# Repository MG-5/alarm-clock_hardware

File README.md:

# alarm-clock_v3
Hardware for alarm clock with VFD display

### Requirements for rev 1.0
* 24V input
* efficient boost converter up to 40V
* control VFD display with multiplexing & dimming
* control 24V CCT-LED strip (cold/neutral/warm white) with PWM
* I²C interface
  * DS3231 as RTC
* connection to ESP (UART)
* battery-backup

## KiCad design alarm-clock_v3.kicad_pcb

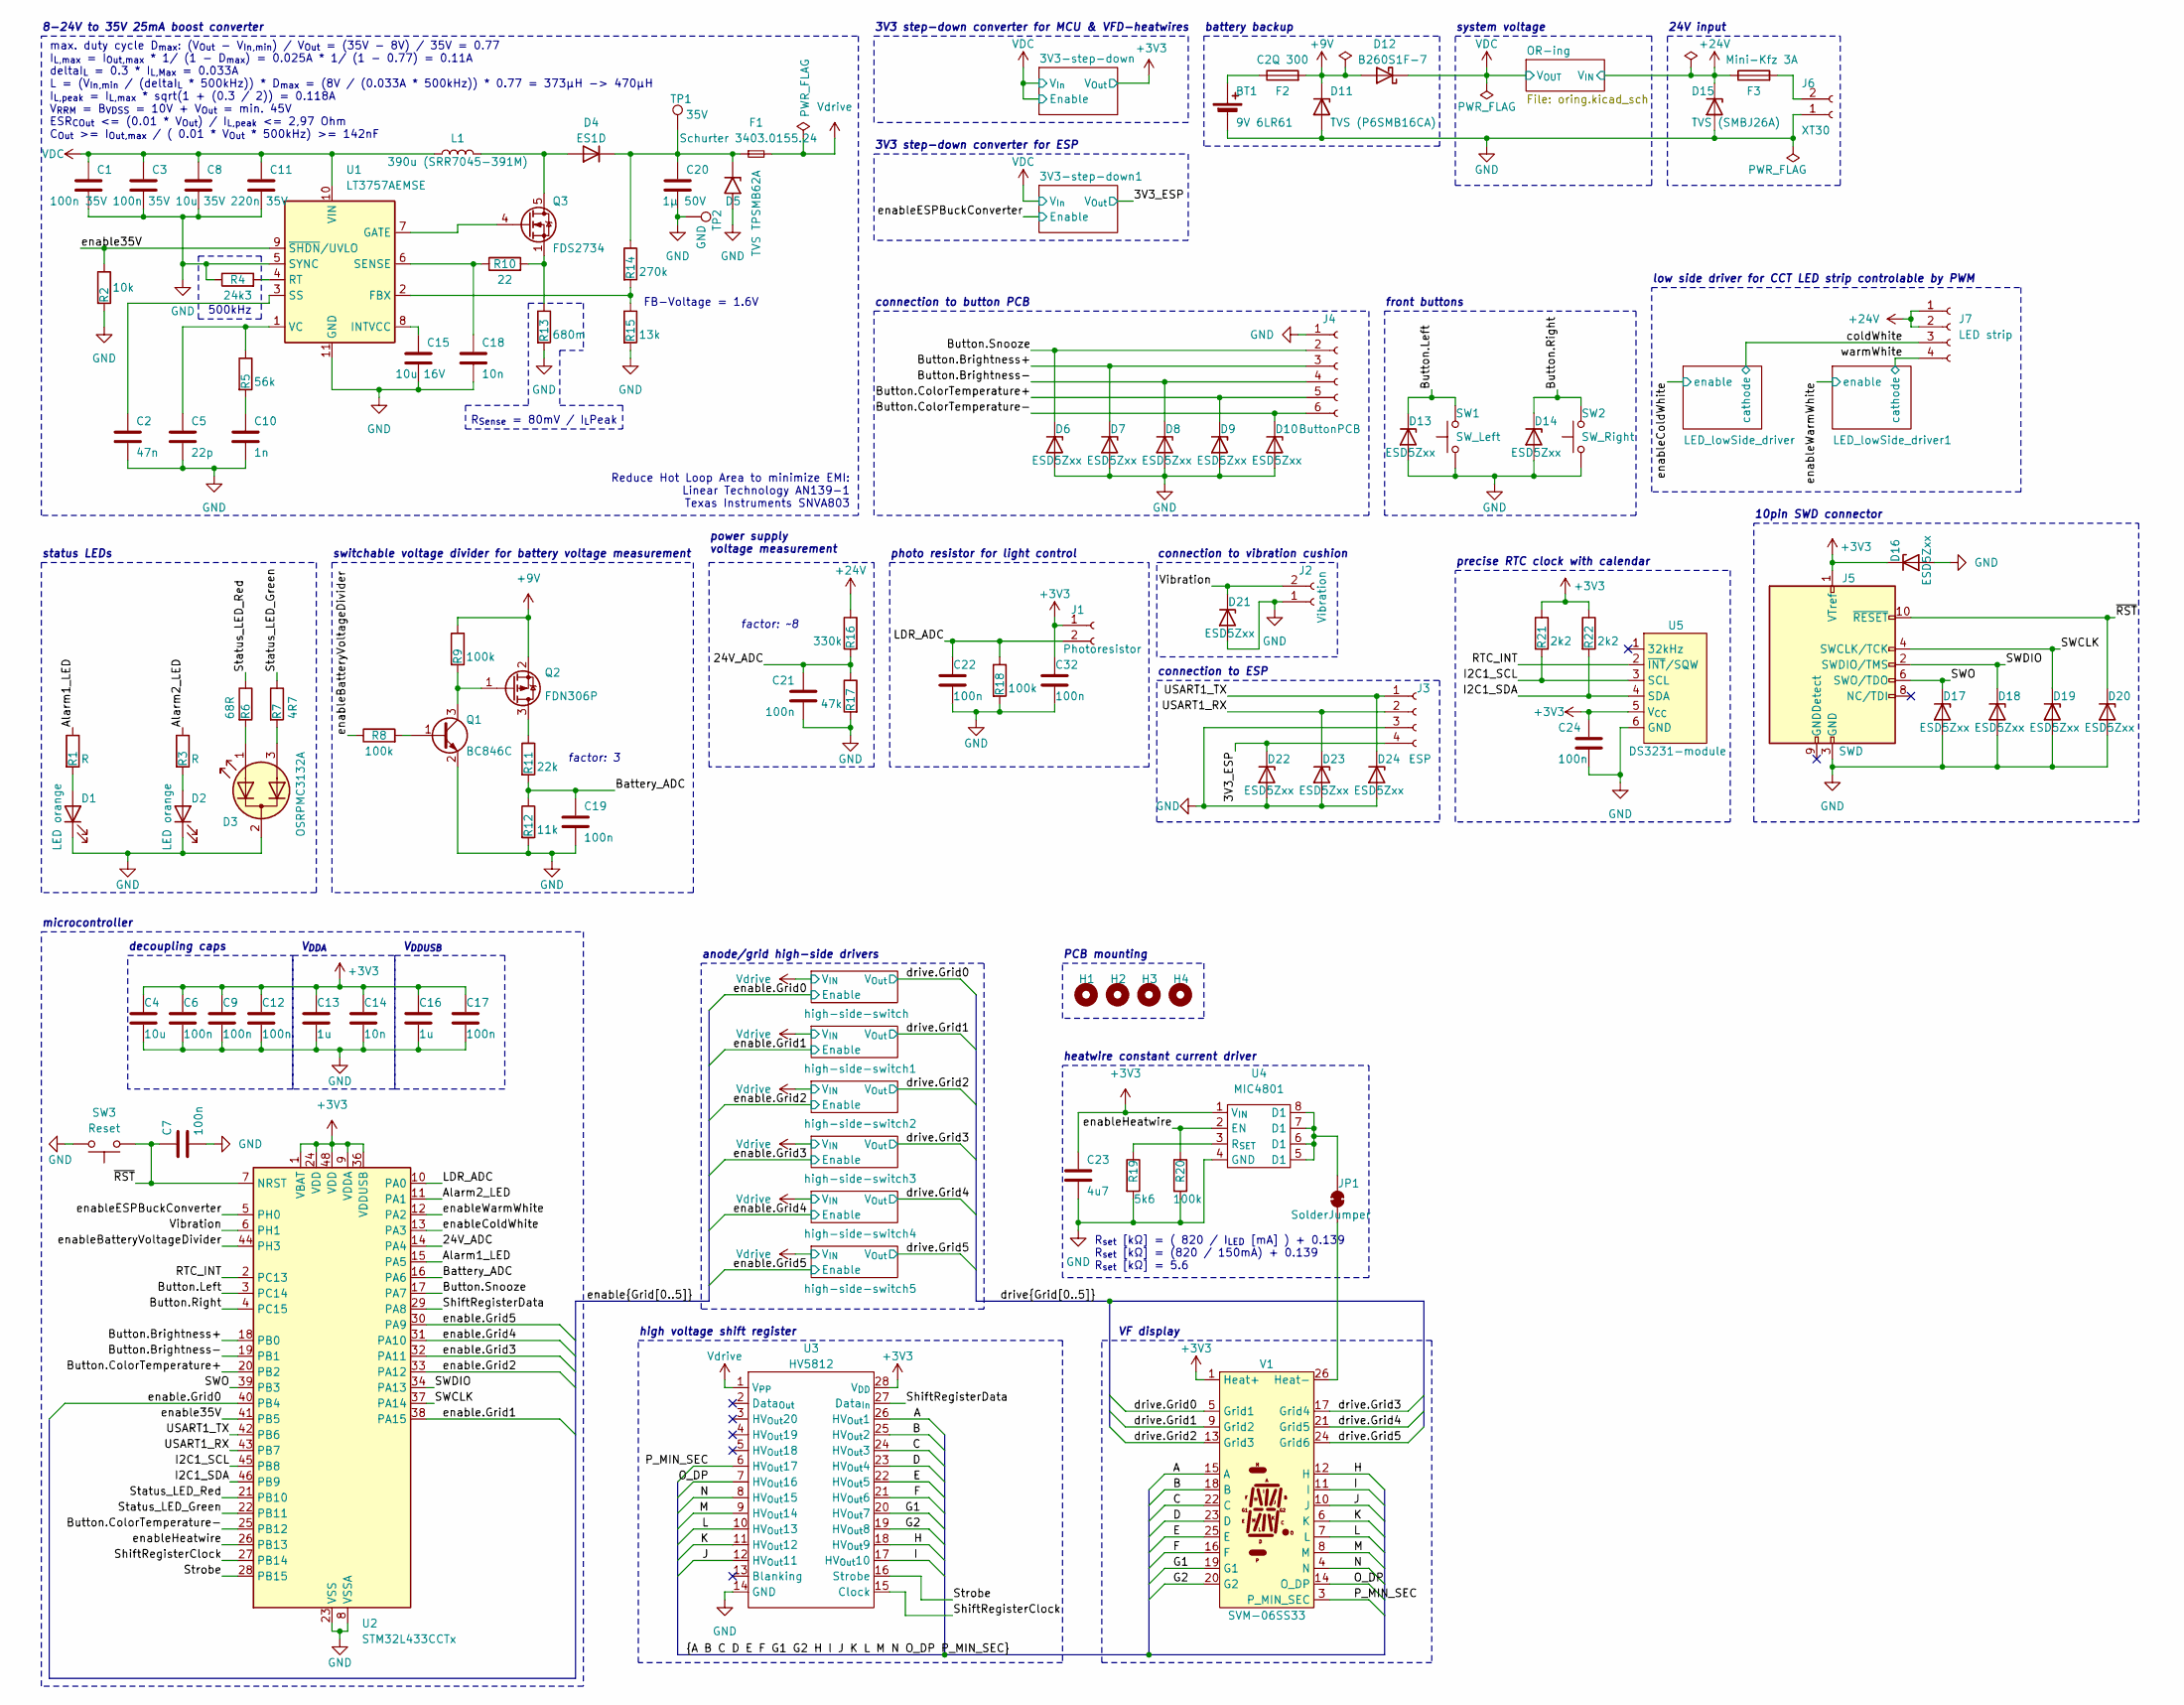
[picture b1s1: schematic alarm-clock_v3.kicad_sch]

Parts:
BT1: 9V 6LR61; Molex_PicoBlade_53047-0210_1x02_P1.25mm_Vertical
C1, C3: 100n 35V; C_0603_1608Metric_Pad1.08x0.95mm_HandSolder
C2: 47n; C_0603_1608Metric_Pad1.08x0.95mm_HandSolder
C4: 10u; C_0805_2012Metric_Pad1.18x1.45mm_HandSolder
C5: 22p; C_0402_1005Metric_Pad0.74x0.62mm_HandSolder
C6, C7, C9, C12, C17, C19, C21, C22, C24, C32: 100n; C_0603_1608Metric_Pad1.08x0.95mm_HandSolder
C8: 10u 35V; C_1206_3216Metric_Pad1.33x1.80mm_HandSolder
C10: 1n; C_0603_1608Metric_Pad1.08x0.95mm_HandSolder
C11: 220n 35V; C_0805_2012Metric_Pad1.18x1.45mm_HandSolder
C13, C16: 1u; C_0603_1608Metric_Pad1.08x0.95mm_HandSolder
C14: 10n; C_0603_1608Metric_Pad1.08x0.95mm_HandSolder
C15: 10u 16V; C_0805_2012Metric_Pad1.18x1.45mm_HandSolder
C18: 10n; C_0805_2012Metric_Pad1.18x1.45mm_HandSolder
C20: 1µ 50V; C_0805_2012Metric_Pad1.18x1.45mm_HandSolder
C23: 4u7; C_0603_1608Metric_Pad1.08x0.95mm_HandSolder
D1, D2: LED orange; PinHeader_1x02_P2.54mm_Vertical
D3: OSRPMC3132A; PinHeader_1x03_P2.54mm_Vertical
D4: ES1D; D_SMA_Handsoldering
D5: TVS TPSMB62A; D_SMF
D6, D7, D8, D9, D10, D13, D14, D16, D17, D18, D19, D20, D21, D22, D23, D24: ESD5Zxx; D_SOD-523
D11: TVS (P6SMB16CA); D_SMB_Handsoldering
D12: B260S1F-7; D_SOD-123
D15: TVS (SMBJ26A); D_SMB_Handsoldering
F1: Schurter 3403.0155.24; Fuse_Schurter_UMT250
F2: C2Q 300; Fuse_0603_1608Metric_Pad1.05x0.95mm_HandSolder
F3: Mini-Kfz 3A; KEYSTONE-FUSE-3557-2
H1, H2, H3, H4: MountingHole; MountingHole_3.2mm_M3_ISO14580
J1: Photoresistor; Molex_PicoBlade_53047-0210_1x02_P1.25mm_Vertical
J2: Vibration; Molex_PicoBlade_53047-0210_1x02_P1.25mm_Vertical
J3: ESP; Molex_PicoBlade_53047-0410_1x04_P1.25mm_Vertical
J4: ButtonPCB; Molex_PicoBlade_53047-0610_1x06_P1.25mm_Vertical
J5: SWD; PinHeader_2x05_P1.27mm_Vertical_SMD
J6: XT30; AMASS_XT30U-M_1x02_P5.0mm_Vertical
J7: LED strip; Molex_PicoBlade_53047-0410_1x04_P1.25mm_Vertical
JP1: SolderJumper; SolderJumper-2_P1.3mm_Open_TrianglePad1.0x1.5mm
L1: 390u (SRR7045-391M); L_7.3x7.3_H4.5
Q1: BC846C; SOT-23_Handsoldering
Q2: FDN306P; SOT-23_Handsoldering
Q3: FDS2734; SOIC-8_3.9x4.9mm_P1.27mm
R1, R3: R; R_0603_1608Metric_Pad0.98x0.95mm_HandSolder
R2: 10k; R_0603_1608Metric_Pad0.98x0.95mm_HandSolder
R4: 24k3; R_0603_1608Metric_Pad0.98x0.95mm_HandSolder
R5: 56k; R_0603_1608Metric_Pad0.98x0.95mm_HandSolder
R6: 68R; R_0603_1608Metric_Pad0.98x0.95mm_HandSolder
R7: 4R7; R_0603_1608Metric_Pad0.98x0.95mm_HandSolder
R8, R9, R18, R20: 100k; R_0603_1608Metric_Pad0.98x0.95mm_HandSolder
R10: 22; R_0603_1608Metric_Pad0.98x0.95mm_HandSolder
R11: 22k; R_0603_1608Metric_Pad0.98x0.95mm_HandSolder
R12: 11k; R_0603_1608Metric_Pad0.98x0.95mm_HandSolder
R13: 680m; R_0603_1608Metric_Pad0.98x0.95mm_HandSolder
R14: 270k; R_0603_1608Metric_Pad0.98x0.95mm_HandSolder
R15: 13k; R_0603_1608Metric_Pad0.98x0.95mm_HandSolder
R16: 330k; R_0603_1608Metric_Pad0.98x0.95mm_HandSolder
R17: 47k; R_0603_1608Metric_Pad0.98x0.95mm_HandSolder
R19: 5k6; R_0603_1608Metric_Pad0.98x0.95mm_HandSolder
R21, R22: 2k2; R_0603_1608Metric_Pad0.98x0.95mm_HandSolder
SW1: SW_Left; SW_SPST_PTS810
SW2: SW_Right; SW_SPST_PTS810
SW3: Reset; SW_SPST_PTS810
TP1: 35V; TestPoint_THTPad_D1.5mm_Drill0.7mm
TP2: GND; TestPoint_THTPad_D1.5mm_Drill0.7mm
U1: LT3757AEMSE; MSOP-10-1EP_3x3mm_P0.5mm_EP1.68x1.88mm
U2: STM32L433CCTx; LQFP-48_7x7mm_P0.5mm
U3: HV5812; SOIC-28W_7.5x17.9mm_P1.27mm
U4: MIC4801; PowerIntegrations_SO-8
U5: DS3231-module
V1: SVM-06SS33

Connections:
+3V3: C4.1, C6.1, C9.1, C12.1, C13.1, C14.1, C16.1, C17.1, C23.1, C24.1, C32.1, D16.1 (K), J1.1, J5.1 (VTref), R21.1, R22.1, U2.1 (VBAT), U2.9 (VDDA), U2.24 (VDD), U2.36 (VDDUSB), U2.48 (VDD), U3.28 (V_{DD}), U4.1 (V_{IN}), U5.5 (V_{CC}), V1.1 (Heat+), V1.2 (Heat+); also elsewhere on the board
+9V: D11.1 (K), D12.2 (A), F2.2, Q2.2 (S), R9.1
+24V: D15.1 (K), F3.1, J7.1, J7.2, R16.1; also elsewhere on the board
/3V3_ESP: D22.1 (K), J3.4; also elsewhere on the board
/24V_ADC: C21.1, R16.2, R17.1, U2.14 (PA4)
/A: U3.26 (HV_{Out}1), V1.15 (A)
/Alarm1_LED: R1.1, U2.15 (PA5)
/Alarm2_LED: R3.1, U2.11 (PA1)
/B: U3.25 (HV_{Out}2), V1.18 (B)
/Battery_ADC: C19.1, R11.2, R12.1, U2.16 (PA6)
/Button.Brightness+: D7.1 (K), J4.3, U2.18 (PB0)
/Button.Brightness-: D8.1 (K), J4.4, U2.19 (PB1)
/Button.ColorTemperature+: D9.1 (K), J4.5, U2.20 (PB2)
/Button.ColorTemperature-: D10.1 (K), J4.6, U2.25 (PB12)
/Button.Left: D13.1 (K), SW1.2, U2.3 (PC14)
/Button.Right: D14.1 (K), SW2.2, U2.4 (PC15)
/Button.Snooze: D6.1 (K), J4.2, U2.17 (PA7)
/C: U3.24 (HV_{Out}3), V1.22 (C)
/D: U3.23 (HV_{Out}4), V1.23 (D)
/E: U3.22 (HV_{Out}5), V1.25 (E)
/F: U3.21 (HV_{Out}6), V1.16 (F)
/G1: U3.20 (HV_{Out}7), V1.19 (G1)
/G2: U3.19 (HV_{Out}8), V1.20 (G2)
/H: U3.18 (HV_{Out}9), V1.12 (H)
/I: U3.17 (HV_{Out}10), V1.11 (I)
/I2C1_SCL: R21.2, U2.45 (PB8), U5.3 (SCL)
/I2C1_SDA: R22.2, U2.46 (PB9), U5.4 (SDA)
/J: U3.12 (HV_{Out}11), V1.10 (J)
/K: U3.11 (HV_{Out}12), V1.6 (K)
/L: U3.10 (HV_{Out}13), V1.7 (L)
/LDR_ADC: C22.1, J1.2, R18.1, U2.10 (PA0)
/M: U3.9 (HV_{Out}14), V1.8 (M)
/N: U3.8 (HV_{Out}15), V1.4 (N)
/O_DP: U3.7 (HV_{Out}16), V1.14 (O_DP)
/P_MIN_SEC: U3.6 (HV_{Out}17), V1.3 (P_MIN_SEC)
/RTC_INT: U2.2 (PC13), U5.2 (~INT/SQW)
/SWCLK: D19.1 (K), J5.4 (SWCLK/TCK), U2.37 (PA14)
/SWDIO: D18.1 (K), J5.2 (SWDIO/TMS), U2.34 (PA13)
/SWO: D17.1 (K), J5.6 (SWO/TDO), U2.39 (PB3)
/ShiftRegisterClock: U2.27 (PB14), U3.15 (Clock)
/ShiftRegisterData: U2.29 (PA8), U3.27 (Data_{In})
/Status_LED_Green: R7.1, U2.22 (PB11)
/Status_LED_Red: R6.1, U2.21 (PB10)
/Strobe: U2.28 (PB15), U3.16 (Strobe)
/USART1_RX: D23.1 (K), J3.2, U2.43 (PB7)
/USART1_TX: D24.1 (K), J3.1, U2.42 (PB6)
/Vibration: D21.1 (K), J2.2, U2.6 (PH1)
/coldWhite: J7.3; also elsewhere on the board
/drive.Grid0: V1.5 (Grid1); also elsewhere on the board
/drive.Grid1: V1.9 (Grid2); also elsewhere on the board
/drive.Grid2: V1.13 (Grid3); also elsewhere on the board
/drive.Grid3: V1.17 (Grid4); also elsewhere on the board
/drive.Grid4: V1.21 (Grid5); also elsewhere on the board
/drive.Grid5: V1.24 (Grid6); also elsewhere on the board
/enable35V: R2.1, U1.9 (~SHDN/UVLO), U2.41 (PB5)
/enable.Grid0: U2.40 (PB4); also elsewhere on the board
/enable.Grid1: U2.38 (PA15); also elsewhere on the board
/enable.Grid2: U2.33 (PA12); also elsewhere on the board
/enable.Grid3: U2.32 (PA11); also elsewhere on the board
/enable.Grid4: U2.31 (PA10); also elsewhere on the board
/enable.Grid5: U2.30 (PA9); also elsewhere on the board
/enableBatteryVoltageDivider: R8.1, U2.44 (PH3)
/enableColdWhite: U2.13 (PA3); also elsewhere on the board
/enableESPBuckConverter: U2.5 (PH0); also elsewhere on the board
/enableHeatwire: R20.1, U2.26 (PB13), U4.2 (EN)
/enableWarmWhite: U2.12 (PA2); also elsewhere on the board
/warmWhite: J7.4; also elsewhere on the board
/~RST: C7.1, D20.1 (K), J5.10 (~RESET), SW3.1, U2.7 (NRST)
GND: BT1.2 (-), C1.2, C2.2, C3.2, C4.2, C5.2, C6.2, C7.2, C8.2, C9.2, C10.2, C11.2, C12.2, C13.2, C14.2, C15.2, C16.2, C17.2, C18.2, C19.2, C20.2, C21.2, C22.2, C23.2, C24.2, C32.2, D1.1 (K), D2.1 (K), D3.2 (K), D5.2 (A2), D6.2 (A), D7.2 (A), D8.2 (A), D9.2 (A), D10.2 (A), D11.2 (A), D13.2 (A), D14.2 (A), D15.2 (A), D16.2 (A), D17.2 (A), D18.2 (A), D19.2 (A), D20.2 (A), D21.2 (A), D22.2 (A), D23.2 (A), D24.2 (A), J2.1, J3.3, J4.1, J5.3 (GND), J5.5 (GND), J6.1, Q1.2 (E), R2.2, R4.1, R12.2, R13.2, R15.2, R17.2, R18.2, R19.2, R20.2, SW1.1, SW2.1, SW3.2, TP2.1, U1.5 (SYNC), U1.11 (GND), U2.8 (VSSA), U2.23 (VSS), U2.35 (VSS), U2.47 (VSS), U3.14 (GND), U4.4 (GND), U5.6 (GND); also elsewhere on the board
unnamed: BT1.1 (+), F2.1
unnamed: C10.1, R5.2
unnamed: D1.2 (A), R1.2
unnamed: D2.2 (A), R3.2
unnamed: D3.1 (A1), R6.2
unnamed: D3.3 (A2), R7.2
unnamed: D4.2 (A), L1.2, Q3.5 (D), Q3.6 (D), Q3.7 (D), Q3.8 (D)
unnamed: C20.1, D4.1 (K), D5.1 (A1), F1.1, R14.1, TP1.1
unnamed: F3.2, J6.2
unnamed: JP1.1 (A), U4.5 (D1), U4.6 (D1), U4.7 (D1), U4.8 (D1)
unnamed: JP1.2 (B), V1.26 (Heat-)
unnamed: Q1.1 (B), R8.2
unnamed: Q1.3 (C), Q2.1 (G), R9.2
unnamed: Q2.3 (D), R11.1
unnamed: Q3.4 (G), U1.7 (GATE)
unnamed: Q3.1 (S), Q3.2 (S), Q3.3 (S), R10.2, R13.1
unnamed: R14.2, R15.1, U1.2 (FBX)
unnamed: C15.1, U1.8 (INTVCC)
unnamed: R4.2, U1.4 (RT)
unnamed: C18.1, R10.1, U1.6 (SENSE)
unnamed: C2.1, U1.3 (SS)
unnamed: C5.1, R5.1, U1.1 (VC)
unnamed: R19.1, U4.3 (R_{SET})
VDC: C1.1, C3.1, C8.1, C11.1, D12.1 (K), L1.1, U1.10 (VIN); also elsewhere on the board
Vdrive: F1.2, U3.1 (V_{PP}); also elsewhere on the board

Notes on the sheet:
24V input
decoupling caps
factor: 3
microcontroller
V_{DDUSB}
factor: ~8
heatwire constant current driver
status LEDs
8-24V to 35V 25mA boost converter
system voltage
connection to ESP
power supply voltage measurement
R_{Sense} = 80mV / I_{L}Peak
3V3 step-down converter for MCU & VFD-heatwires
front buttons
Reduce Hot Loop Area to minimize EMI: Linear Technology AN139-1 Texas Instruments SNVA803
PCB mounting
battery backup
connection to button PCB
precise RTC clock with calendar
photo resistor for light control
low side driver for CCT LED strip controlable by PWM
3V3 step-down converter for ESP
500kHz
high voltage shift register
FB-Voltage = 1.6V
anode/grid high-side drivers
10pin SWD connector
R_{set} [kΩ] = ( 820 / I_{LED} [mA] ) + 0.139 R_{set} [kΩ] = (820 / 150mA) + 0.139 R_{set} [kΩ] = 5.6
connection to vibration cushion
VF display
switchable voltage divider for battery voltage measurement
max. duty cycle D_{max}: (V_{Out} - V_{In,min}) / V_{Out} = (35V - 8V) / 35V = 0.77 I_{L,max} = I_{Out,max} * 1/ (1 - D_{max}) = 0.025A * 1/ (1 - 0.77) = 0.11A deltaI_{L} = 0.3 * I_{L,Max} = 0.033A L = (V_{In,min} / (deltaI_{L} * 500kHz)) * D_{max} = (8V / (0.033A * 500kHz)) * 0.77 = 373µH -> 470µH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
V_{DDA}

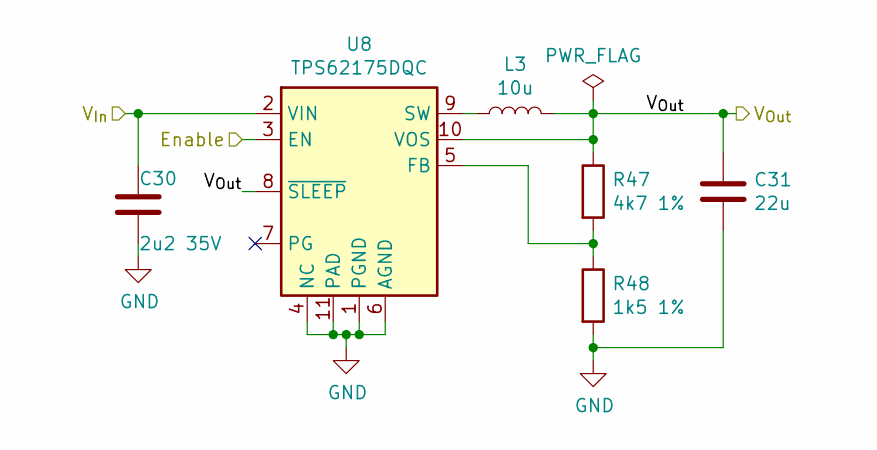
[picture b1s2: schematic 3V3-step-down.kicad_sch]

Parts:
C30: 2u2 35V; C_0603_1608Metric_Pad1.08x0.95mm_HandSolder
C31: 22u; C_0805_2012Metric_Pad1.18x1.45mm_HandSolder
L3: 10u; L_1210_3225Metric
R47: 4k7 1%; R_0603_1608Metric_Pad0.98x0.95mm_HandSolder
R48: 1k5 1%; R_0603_1608Metric_Pad0.98x0.95mm_HandSolder
U8: TPS62175DQC; WSON-10-1EP_2x3mm_P0.5mm_EP0.84x2.4mm_ThermalVias

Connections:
/3V3_ESP: C31.1, L3.2, R47.1, U8.8 (~SLEEP), U8.10 (VOS); also elsewhere on the board
/enableESPBuckConverter: U8.3 (EN); also elsewhere on the board
GND: C30.2, C31.2, R48.2, U8.1 (PGND), U8.4 (NC), U8.6 (AGND), U8.11 (PAD); also elsewhere on the board
unnamed: R47.2, R48.1, U8.5 (FB)
unnamed: L3.1, U8.9 (SW)
VDC: C30.1, U8.2 (VIN); also elsewhere on the board

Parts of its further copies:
C28: 2u2 35V; C_0603_1608Metric_Pad1.08x0.95mm_HandSolder
C29: 22u; C_0805_2012Metric_Pad1.18x1.45mm_HandSolder
L2: 10u; L_1210_3225Metric
R45: 4k7 1%; R_0603_1608Metric_Pad0.98x0.95mm_HandSolder
R46: 1k5 1%; R_0603_1608Metric_Pad0.98x0.95mm_HandSolder
U7: TPS62175DQC; WSON-10-1EP_2x3mm_P0.5mm_EP0.84x2.4mm_ThermalVias

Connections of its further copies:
+3V3: C29.1, L2.2, R45.1, U7.8 (~SLEEP), U7.10 (VOS); also elsewhere on the board
GND: C28.2, C29.2, R46.2, U7.1 (PGND), U7.4 (NC), U7.6 (AGND), U7.11 (PAD); also elsewhere on the board
unnamed: R45.2, R46.1, U7.5 (FB)
unnamed: L2.1, U7.9 (SW)
VDC: C28.1, U7.2 (VIN), U7.3 (EN); also elsewhere on the board

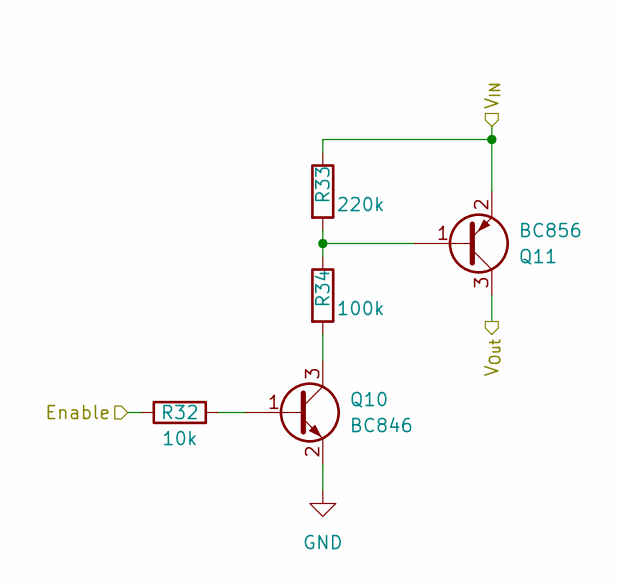
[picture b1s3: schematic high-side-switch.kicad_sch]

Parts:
Q10: BC846; SOT-23_Handsoldering
Q11: BC856; SOT-23_Handsoldering
R32: 10k; R_0603_1608Metric_Pad0.98x0.95mm_HandSolder
R33: 220k; R_0603_1608Metric_Pad0.98x0.95mm_HandSolder
R34: 100k; R_0603_1608Metric_Pad0.98x0.95mm_HandSolder

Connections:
/drive.Grid3: Q11.3 (C); also elsewhere on the board
/enable.Grid3: R32.1; also elsewhere on the board
GND: Q10.2 (E); also elsewhere on the board
unnamed: Q10.1 (B), R32.2
unnamed: Q10.3 (C), R34.2
unnamed: Q11.1 (B), R33.2, R34.1
Vdrive: Q11.2 (E), R33.1; also elsewhere on the board

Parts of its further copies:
Q4, Q6, Q8, Q12, Q14: BC846; SOT-23_Handsoldering
Q5, Q7, Q9, Q13, Q15: BC856; SOT-23_Handsoldering
R23, R26, R29, R35, R38: 10k; R_0603_1608Metric_Pad0.98x0.95mm_HandSolder
R24, R27, R30, R36, R39: 220k; R_0603_1608Metric_Pad0.98x0.95mm_HandSolder
R25, R28, R31, R37, R40: 100k; R_0603_1608Metric_Pad0.98x0.95mm_HandSolder

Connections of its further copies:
/drive.Grid0: Q5.3 (C); also elsewhere on the board
/drive.Grid1: Q7.3 (C); also elsewhere on the board
/drive.Grid2: Q9.3 (C); also elsewhere on the board
/drive.Grid4: Q13.3 (C); also elsewhere on the board
/drive.Grid5: Q15.3 (C); also elsewhere on the board
/enable.Grid0: R23.1; also elsewhere on the board
/enable.Grid1: R26.1; also elsewhere on the board
/enable.Grid2: R29.1; also elsewhere on the board
/enable.Grid4: R35.1; also elsewhere on the board
/enable.Grid5: R38.1; also elsewhere on the board
GND: Q4.2 (E), Q6.2 (E), Q8.2 (E), Q12.2 (E), Q14.2 (E); also elsewhere on the board
unnamed: Q4.1 (B), R23.2
unnamed: Q4.3 (C), R25.2
unnamed: Q5.1 (B), R24.2, R25.1
unnamed: Q6.1 (B), R26.2
unnamed: Q6.3 (C), R28.2
unnamed: Q7.1 (B), R27.2, R28.1
unnamed: Q8.1 (B), R29.2
unnamed: Q8.3 (C), R31.2
unnamed: Q9.1 (B), R30.2, R31.1
unnamed: Q12.1 (B), R35.2
unnamed: Q12.3 (C), R37.2
unnamed: Q13.1 (B), R36.2, R37.1
unnamed: Q14.1 (B), R38.2
unnamed: Q14.3 (C), R40.2
unnamed: Q15.1 (B), R39.2, R40.1
Vdrive: Q5.2 (E), Q7.2 (E), Q9.2 (E), Q13.2 (E), Q15.2 (E), R24.1, R27.1, R30.1, R36.1, R39.1; also elsewhere on the board

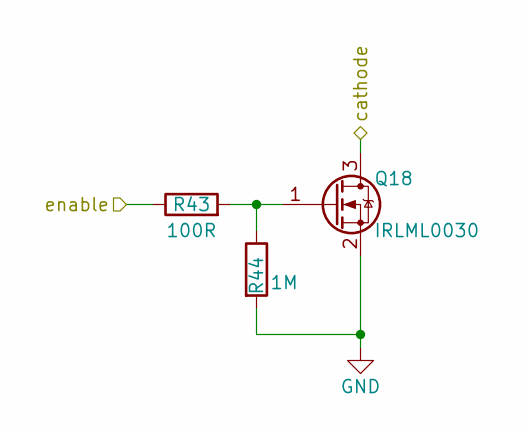
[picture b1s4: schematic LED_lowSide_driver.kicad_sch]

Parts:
Q18: IRLML0030; SOT-23_Handsoldering
R43: 100R; R_0603_1608Metric_Pad0.98x0.95mm_HandSolder
R44: 1M; R_0603_1608Metric_Pad0.98x0.95mm_HandSolder

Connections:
/enableWarmWhite: R43.1; also elsewhere on the board
/warmWhite: Q18.3 (D); also elsewhere on the board
GND: Q18.2 (S), R44.2; also elsewhere on the board
unnamed: Q18.1 (G), R43.2, R44.1

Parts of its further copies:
Q17: IRLML0030; SOT-23_Handsoldering
R41: 100R; R_0603_1608Metric_Pad0.98x0.95mm_HandSolder
R42: 1M; R_0603_1608Metric_Pad0.98x0.95mm_HandSolder

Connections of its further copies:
/coldWhite: Q17.3 (D); also elsewhere on the board
/enableColdWhite: R41.1; also elsewhere on the board
GND: Q17.2 (S), R42.2; also elsewhere on the board
unnamed: Q17.1 (G), R41.2, R42.1

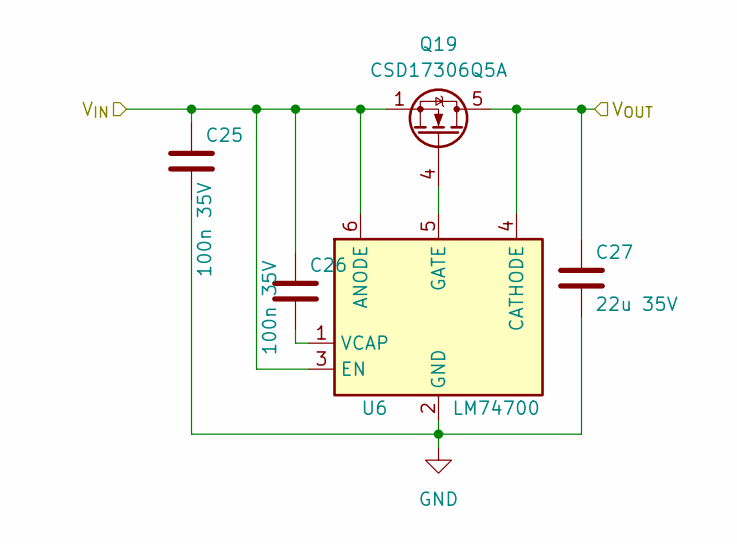
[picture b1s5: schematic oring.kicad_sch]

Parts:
C25, C26: 100n 35V; C_0603_1608Metric_Pad1.08x0.95mm_HandSolder
C27: 22u 35V; C_0805_2012Metric_Pad1.18x1.45mm_HandSolder
Q19: CSD17306Q5A; TDSON-8-1
U6: LM74700; SOT-23-6

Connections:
+24V: C25.1, C26.1, Q19.1 (S), Q19.2 (S), Q19.3 (S), U6.3 (EN), U6.6 (ANODE); also elsewhere on the board
GND: C25.2, C27.2, U6.2 (GND); also elsewhere on the board
unnamed: Q19.4 (G), U6.5 (GATE)
unnamed: C26.2, U6.1 (VCAP)
VDC: C27.1, Q19.5 (D), U6.4 (CATHODE); also elsewhere on the board

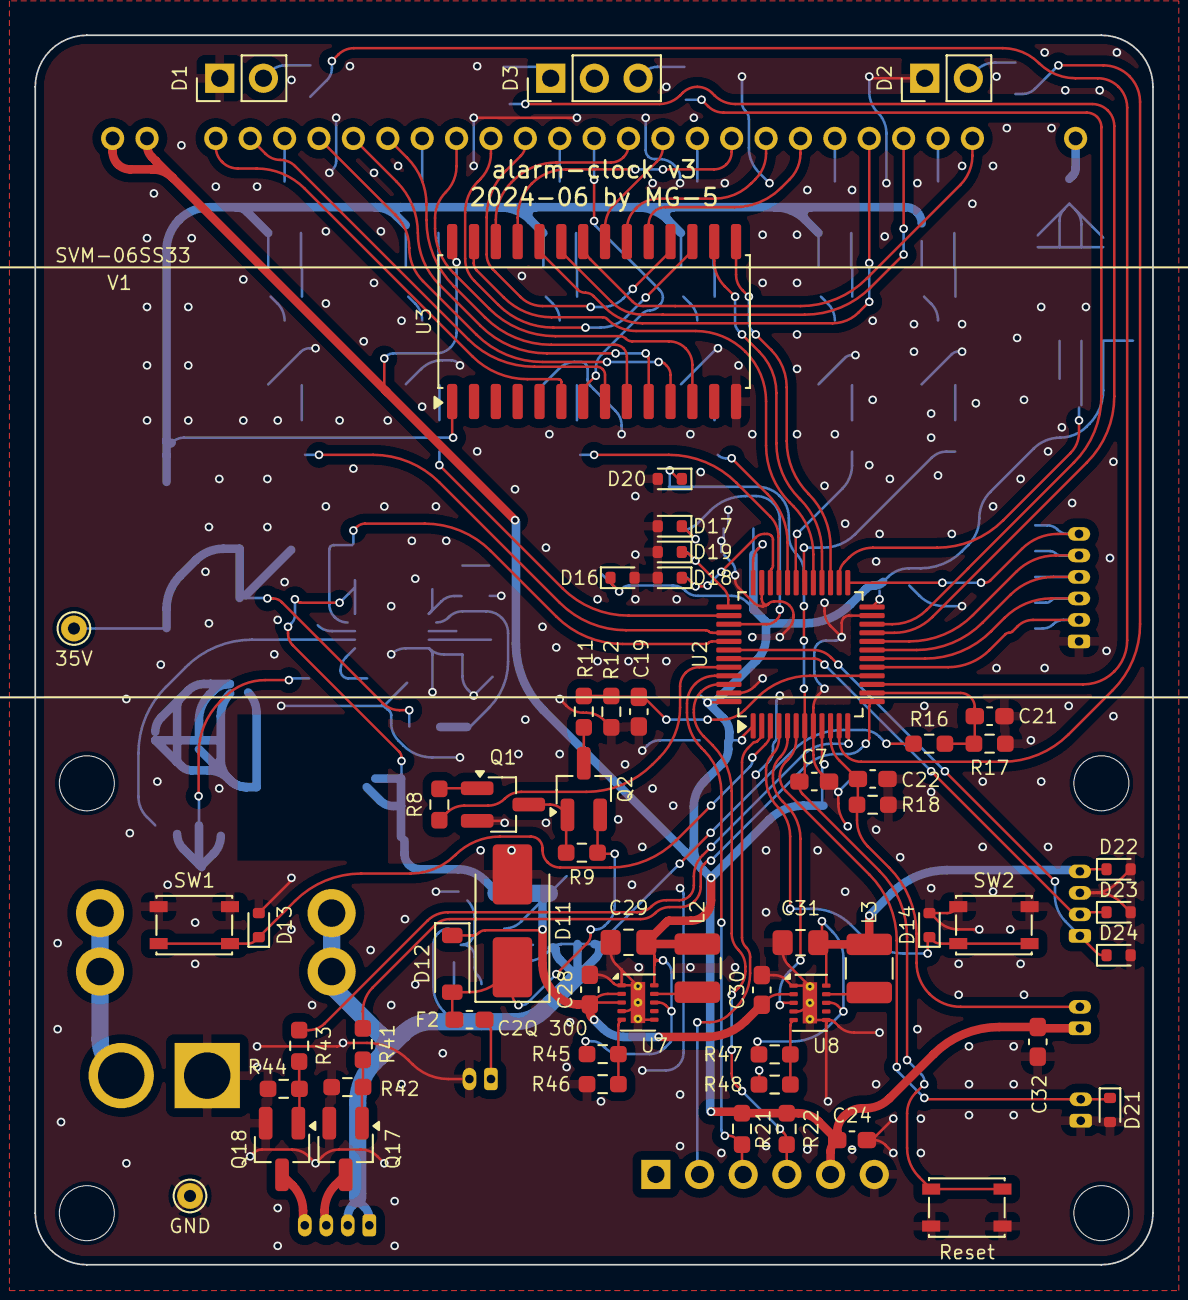
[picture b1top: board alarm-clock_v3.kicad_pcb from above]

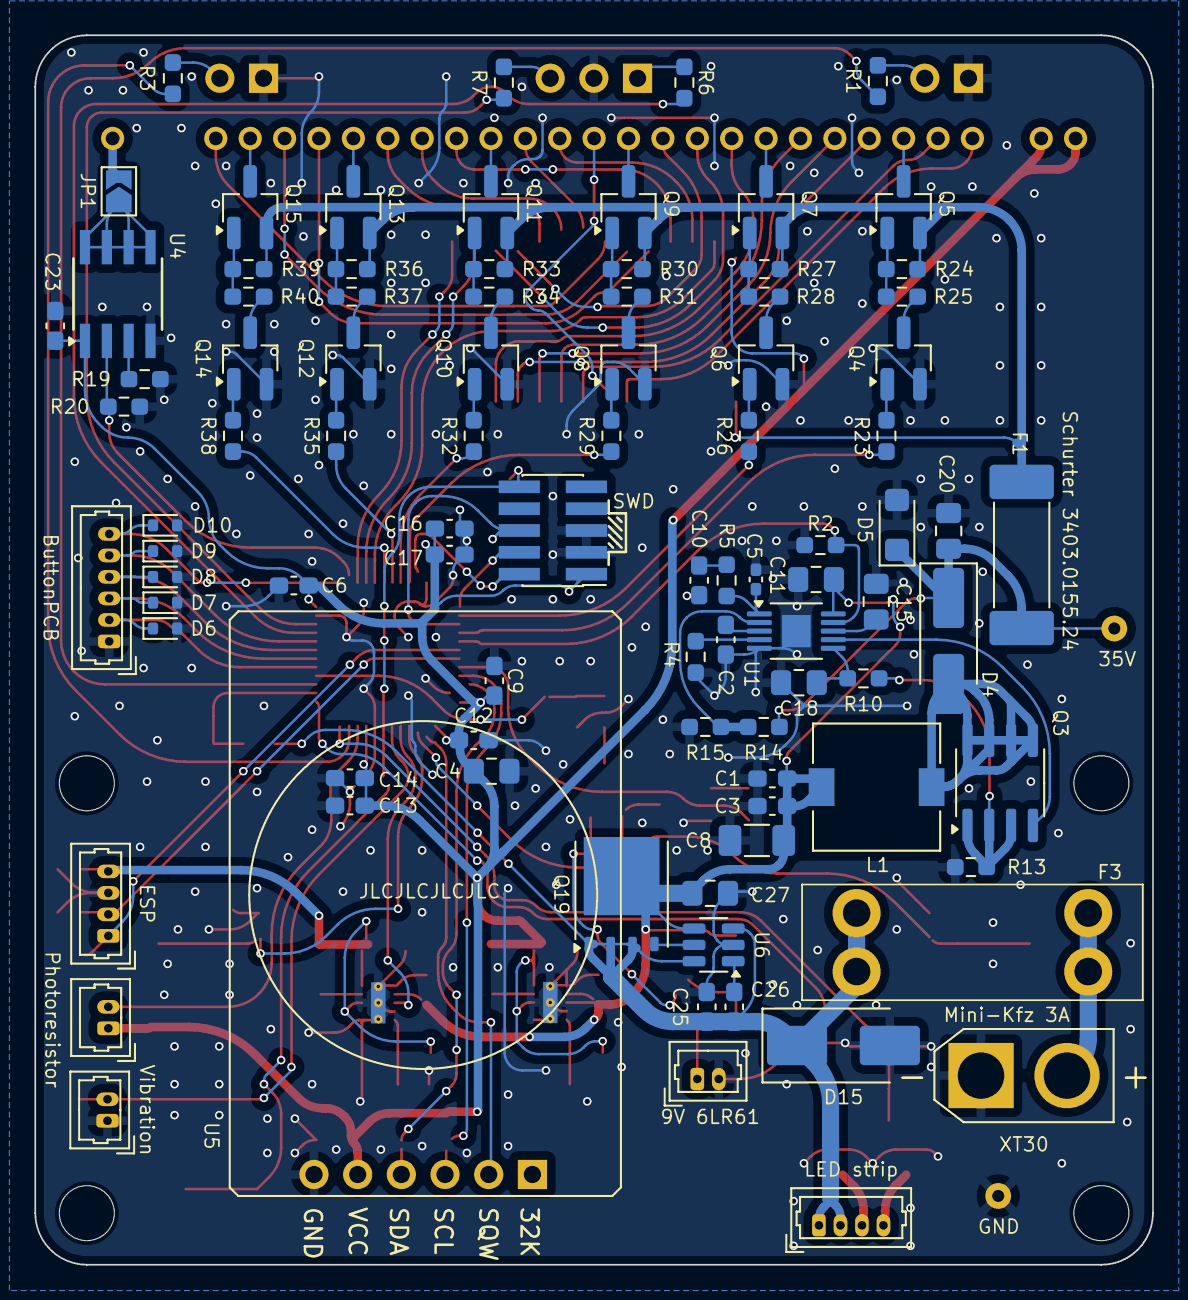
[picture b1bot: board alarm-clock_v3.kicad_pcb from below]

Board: 2 copper layers, 65.0 x 71.5 mm, 155 parts (91 on the bottom side), 120 nets.

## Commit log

2024-05-05 Add SVM-06SS33 VFD display
2024-06-09 Add schematic
2024-06-09 Add PCB
2024-06-09 Polish
2024-06-13 Gerber settings
